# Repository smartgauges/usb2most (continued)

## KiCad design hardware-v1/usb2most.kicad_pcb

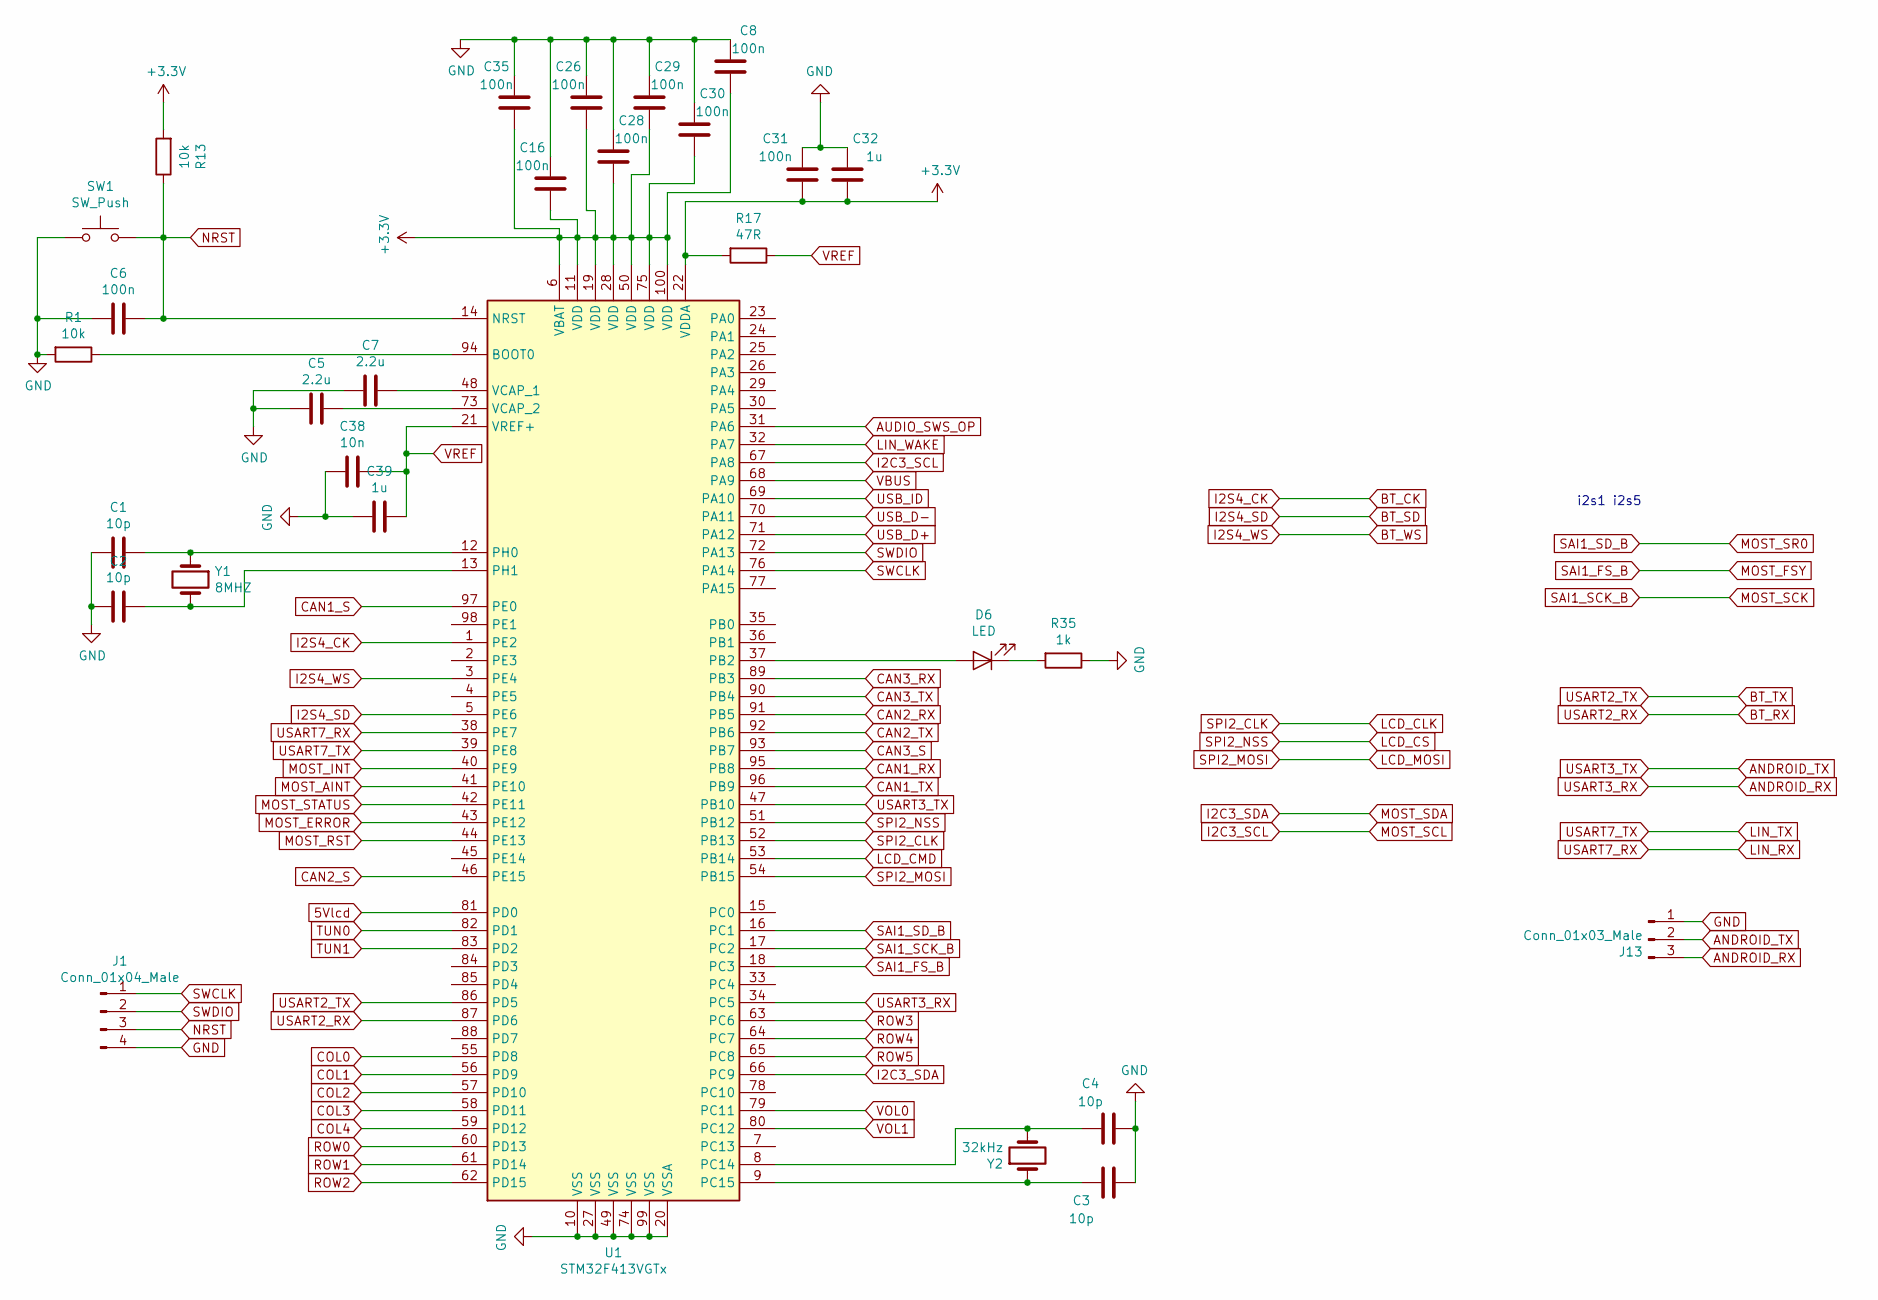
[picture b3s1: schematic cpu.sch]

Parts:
C1, C2, C3, C4: 10p; C_0805_2012Metric
C5, C7: 2.2u; C_1206_3216Metric
C6, C8, C16, C26, C28, C29, C30, C31, C35: 100n; C_0805_2012Metric
C32, C39: 1u; C_1206_3216Metric
C38: 10n; C_0805_2012Metric
D6: LED; R_0805_2012Metric
J1: Conn_01x04_Male; PinSocket_1x04_P2.54mm_Vertical
J13: Conn_01x03_Male; PinSocket_1x03_P2.54mm_Vertical
R1, R13: 10k; R_0805_2012Metric
R17: 47R; R_0805_2012Metric
R35: 1k; R_0805_2012Metric
SW1: SW_Push; SW_Push_1P1T_NO_6x6mm_H9.5mm
U1: STM32F413VGTx; LQFP-100_14x14mm_P0.5mm
Y1: 8MHZ; Crystal_HC49-U_Vertical
Y2: 32kHz; Crystal_C26-LF_D2.1mm_L6.5mm_Vertical

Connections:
5Vlcd: U1.81 (PD0); also elsewhere on the board
+3V3: C8.1, C16.1, C26.1, C28.1, C29.1, C30.1, C31.1, C32.1, C35.1, R13.2, R17.2, U1.6 (VBAT), U1.11 (VDD), U1.19 (VDD), U1.22 (VDDA), U1.28 (VDD), U1.50 (VDD), U1.75 (VDD), U1.100 (VDD); also elsewhere on the board
ANDROID_RX: J13.3, U1.34 (PC5)
ANDROID_TX: J13.2, U1.47 (PB10)
AUDIO_SWS_OP: U1.31 (PA6); also elsewhere on the board
BT_CK: U1.1 (PE2); also elsewhere on the board
BT_RX: U1.87 (PD6); also elsewhere on the board
BT_SD: U1.5 (PE6); also elsewhere on the board
BT_TX: U1.86 (PD5); also elsewhere on the board
BT_WS: U1.3 (PE4); also elsewhere on the board
CAN1_RX: U1.95 (PB8); also elsewhere on the board
CAN1_S: U1.97 (PE0); also elsewhere on the board
CAN1_TX: U1.96 (PB9); also elsewhere on the board
CAN2_RX: U1.91 (PB5); also elsewhere on the board
CAN2_S: U1.46 (PE15); also elsewhere on the board
CAN2_TX: U1.92 (PB6); also elsewhere on the board
CAN3_RX: U1.89 (PB3); also elsewhere on the board
CAN3_S: U1.93 (PB7); also elsewhere on the board
CAN3_TX: U1.90 (PB4); also elsewhere on the board
COL0: U1.55 (PD8); also elsewhere on the board
COL1: U1.56 (PD9); also elsewhere on the board
COL2: U1.57 (PD10); also elsewhere on the board
COL3: U1.58 (PD11); also elsewhere on the board
COL4: U1.59 (PD12); also elsewhere on the board
GND: C1.2, C2.2, C3.2, C4.2, C5.2, C6.2, C7.2, C8.2, C16.2, C26.2, C28.2, C29.2, C30.2, C31.2, C32.2, C35.2, C38.2, C39.2, J1.4, J13.1, R1.2, R35.1, SW1.1, U1.10 (VSS), U1.20 (VSSA), U1.27 (VSS), U1.49 (VSS), U1.74 (VSS), U1.99 (VSS); also elsewhere on the board
I2C1_SCL: U1.67 (PA8); also elsewhere on the board
I2C1_SDA: U1.66 (PC9); also elsewhere on the board
LCD_CLK: U1.52 (PB13); also elsewhere on the board
LCD_CMD: U1.53 (PB14); also elsewhere on the board
LCD_CS: U1.51 (PB12); also elsewhere on the board
LCD_MOSI: U1.54 (PB15); also elsewhere on the board
LIN_RX: U1.38 (PE7); also elsewhere on the board
LIN_TX: U1.39 (PE8); also elsewhere on the board
LIN_WAKE: U1.32 (PA7); also elsewhere on the board
MOST_AINT: U1.41 (PE10); also elsewhere on the board
MOST_ERROR: U1.43 (PE12); also elsewhere on the board
MOST_FSY: U1.18 (PC3); also elsewhere on the board
MOST_INT: U1.40 (PE9); also elsewhere on the board
MOST_RST: U1.44 (PE13); also elsewhere on the board
MOST_SCK: U1.17 (PC2); also elsewhere on the board
MOST_SR0: U1.16 (PC1); also elsewhere on the board
MOST_STATUS: U1.42 (PE11); also elsewhere on the board
NRST: C6.1, J1.3, R13.1, SW1.2, U1.14 (NRST)
unnamed: C1.1, U1.12 (PH0), Y1.1
unnamed: C2.1, U1.13 (PH1), Y1.2
unnamed: C3.1, U1.9 (PC15), Y2.1
unnamed: C4.1, U1.8 (PC14), Y2.2
unnamed: C5.1, U1.73 (VCAP_2)
unnamed: C7.1, U1.48 (VCAP_1)
unnamed: D6.1 (K), R35.2
unnamed: D6.2 (A), U1.37 (PB2)
unnamed: R1.1, U1.94 (BOOT0)
ROW0: U1.60 (PD13); also elsewhere on the board
ROW1: U1.61 (PD14); also elsewhere on the board
ROW2: U1.62 (PD15); also elsewhere on the board
ROW3: U1.63 (PC6); also elsewhere on the board
ROW4: U1.64 (PC7); also elsewhere on the board
ROW5: U1.65 (PC8); also elsewhere on the board
SWCLK: J1.1, U1.76 (PA14)
SWDIO: J1.2, U1.72 (PA13)
TUN0: U1.82 (PD1); also elsewhere on the board
TUN1: U1.83 (PD2); also elsewhere on the board
USB_D+: U1.71 (PA12); also elsewhere on the board
USB_D-: U1.70 (PA11); also elsewhere on the board
USB_ID: U1.69 (PA10); also elsewhere on the board
VBUS: U1.68 (PA9); also elsewhere on the board
VOL0: U1.79 (PC11); also elsewhere on the board
VOL1: U1.80 (PC12); also elsewhere on the board
VREF: C38.1, C39.1, R17.1, U1.21 (VREF+)

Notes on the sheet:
i2s1 i2s5

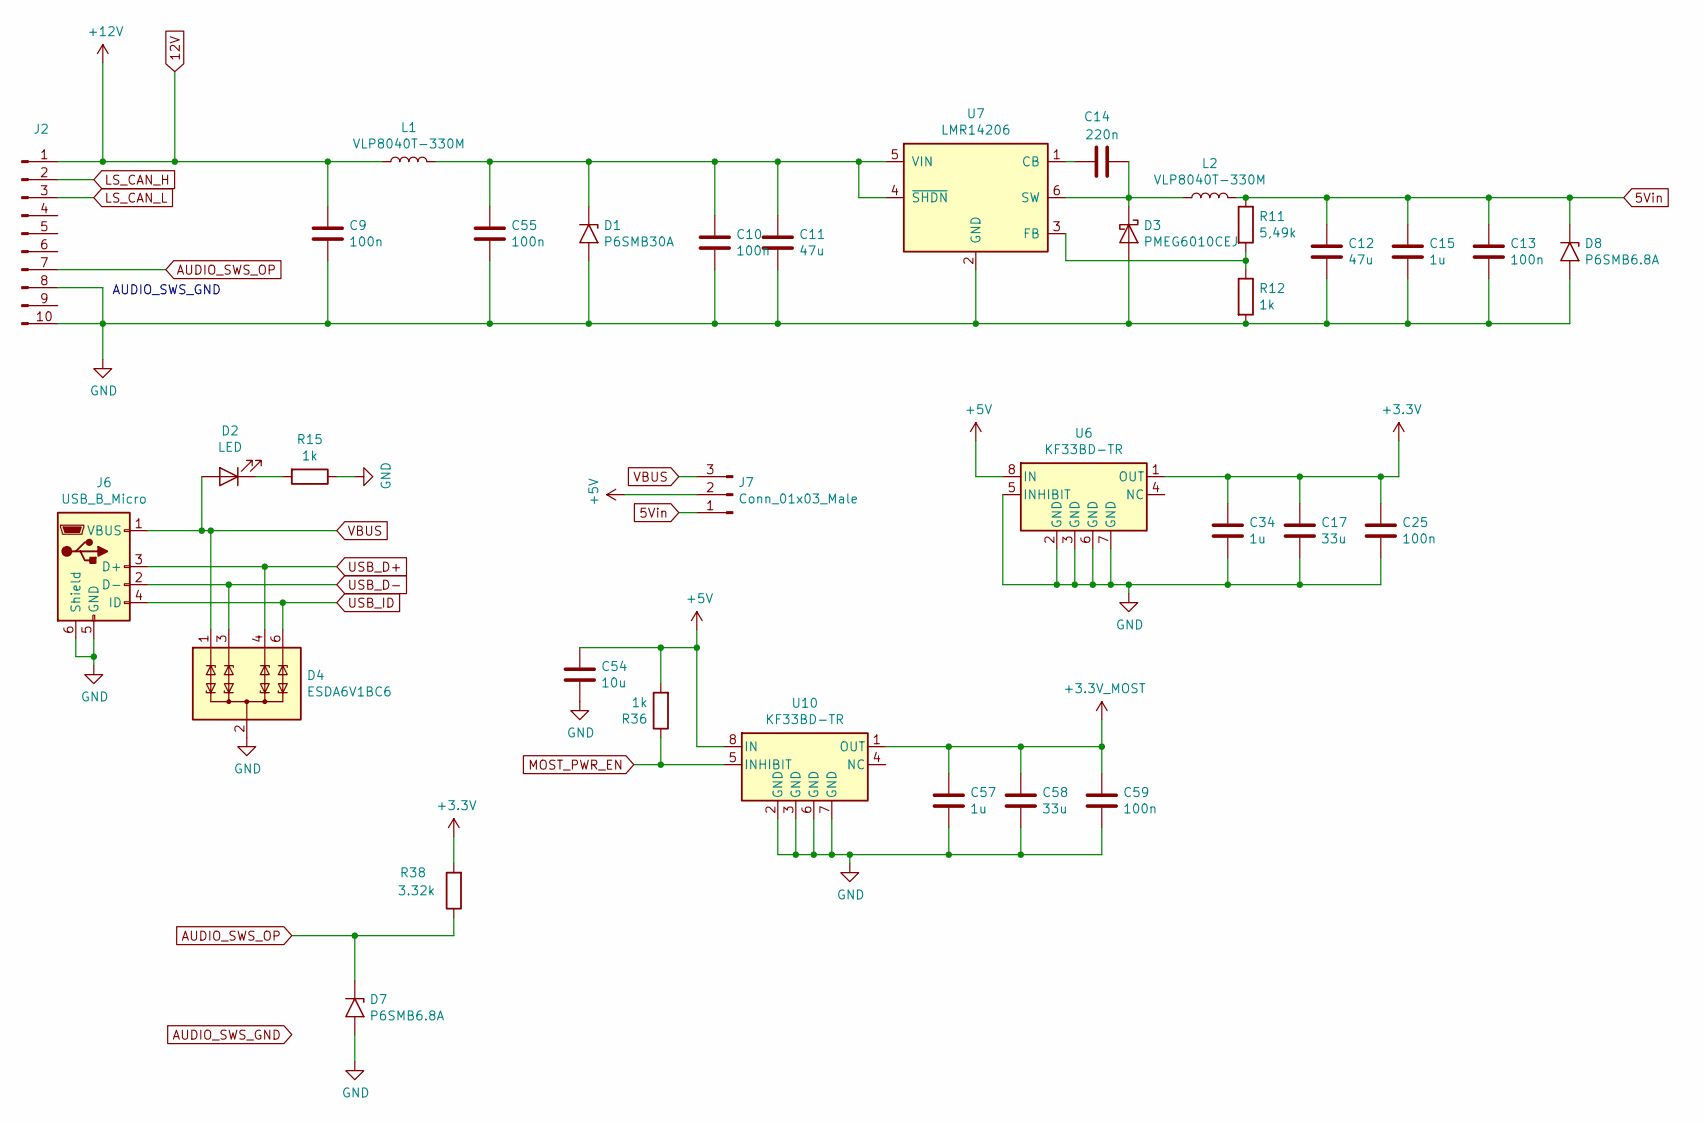
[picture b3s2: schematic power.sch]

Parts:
C9, C10, C13, C25, C55, C59: 100n; C_0805_2012Metric
C11, C12: 47u; C_1206_3216Metric
C14: 220n; C_0805_2012Metric
C15, C34, C57: 1u; C_1206_3216Metric
C17, C58: 33u; C_1206_3216Metric
C54: 10u; C_1206_3216Metric
D1: P6SMB30A; D_SMB
D2: LED; R_0805_2012Metric
D3: PMEG6010CEJ; D_SOD-323
D4: ESDA6V1BC6; SOT-23-6
D7, D8: P6SMB6.8A; D_SMB
J2: Conn_01x10_Male; IL-AG5-10P-S3L2
J6: USB_B_Micro; USB_Micro-B_Molex-105133-0031
J7: Conn_01x03_Male; PinSocket_1x03_P2.54mm_Vertical
L1, L2: VLP8040T-330M; L_TDK_VLP8040
R11: 5,49k; R_0805_2012Metric
R12, R15, R36: 1k; R_0805_2012Metric
R38: 3.32k; R_0805_2012Metric
U6, U10: KF33BD-TR; SO-8_5.3x6.2mm_P1.27mm
U7: LMR14206; SOT-23-6

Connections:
5Vin: C12.1, C13.1, C15.1, D8.1 (A1), J7.1, L2.2, R11.1
12V: C9.1, J2.1, L1.1; also elsewhere on the board
+3.3_MOST: C57.1, C58.1, C59.1, U10.1 (OUT); also elsewhere on the board
+3V3: C17.1, C25.1, C34.1, R38.2, U6.1 (OUT); also elsewhere on the board
+5V: C54.1, J7.2, R36.2, U6.8 (IN), U10.8 (IN); also elsewhere on the board
AUDIO_SWS_OP: D7.1 (A1), J2.7, R38.1; also elsewhere on the board
GND: C9.2, C10.2, C11.2, C12.2, C13.2, C15.2, C17.2, C25.2, C34.2, C54.2, C55.2, C57.2, C58.2, C59.2, D1.2 (A2), D3.2 (A), D4.2 (COM), D4.5 (COM), D7.2 (A2), D8.2 (A2), J2.8, J2.10, J6.5 (GND), J6.6 (Shield), R12.2, R15.1, U6.2 (GND), U6.3 (GND), U6.5 (INHIBIT), U6.6 (GND), U6.7 (GND), U7.2 (GND), U10.2 (GND), U10.3 (GND), U10.6 (GND), U10.7 (GND); also elsewhere on the board
LS_CAN_H: J2.2; also elsewhere on the board
LS_CAN_L: J2.3; also elsewhere on the board
MOST_PWR_EN: R36.1, U10.5 (INHIBIT)
unnamed: C10.1, C11.1, C55.1, D1.1 (A1), L1.2, U7.4 (~SHDN), U7.5 (VIN)
unnamed: C14.1, U7.1 (CB)
unnamed: C14.2, D3.1 (K), L2.1, U7.6 (SW)
unnamed: D2.1 (K), R15.2
unnamed: R11.2, R12.1, U7.3 (FB)
USB_D+: D4.4 (TVS3), J6.3 (D+); also elsewhere on the board
USB_D-: D4.3 (TVS2), J6.2 (D-); also elsewhere on the board
USB_ID: D4.6 (TVS4), J6.4 (ID); also elsewhere on the board
VBUS: D2.2 (A), D4.1 (TVS1), J6.1 (VBUS), J7.3; also elsewhere on the board

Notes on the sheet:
AUDIO_SWS_GND

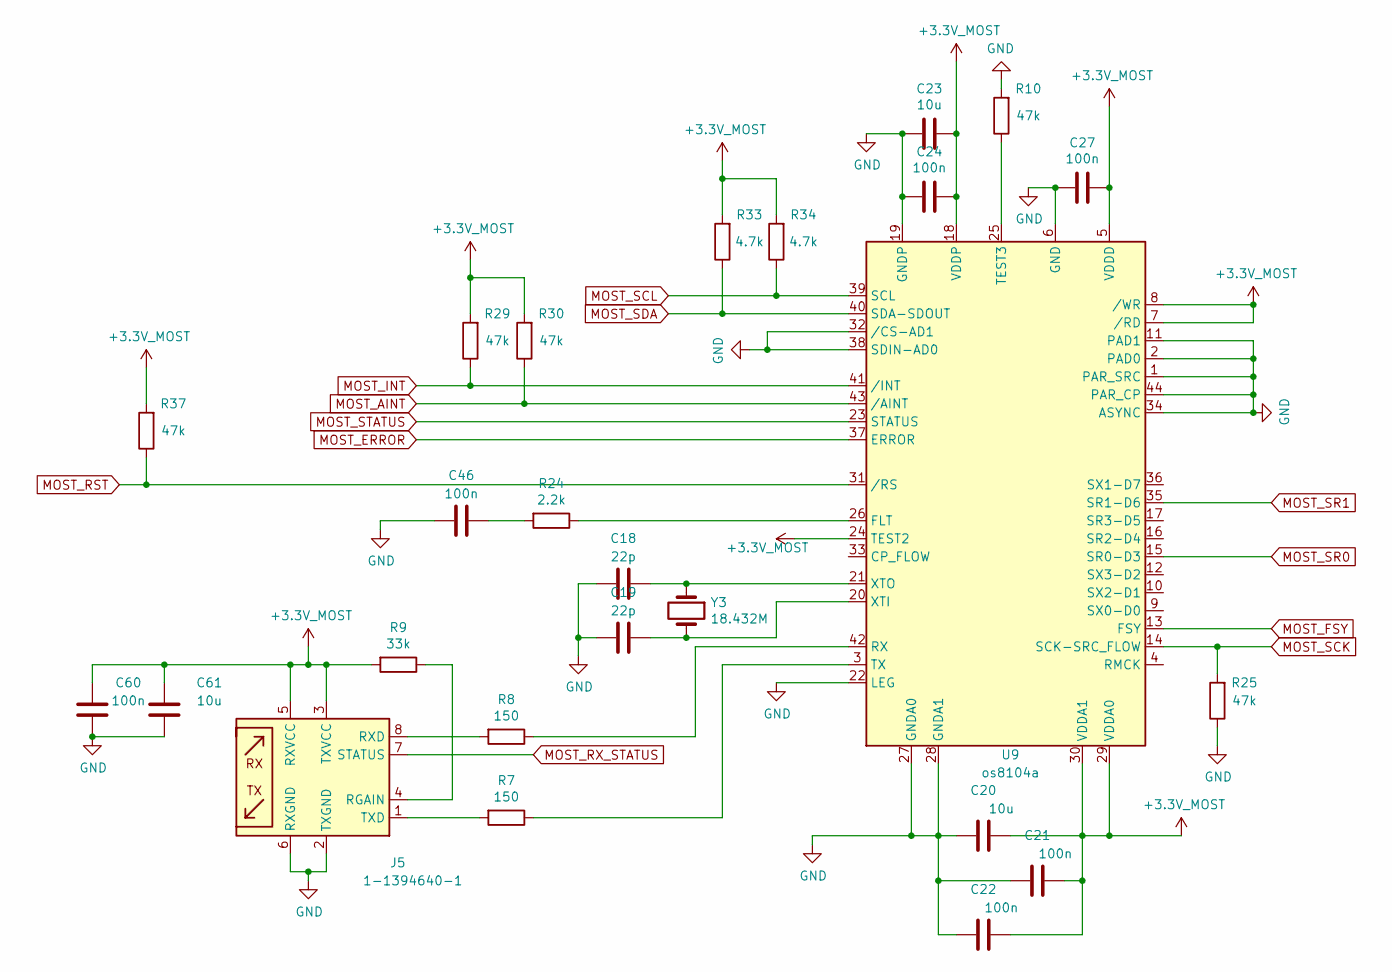
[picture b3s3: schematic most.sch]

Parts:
C18, C19: 22p; C_0805_2012Metric
C20, C23, C61: 10u; C_1206_3216Metric
C21, C22, C24, C27, C46, C60: 100n; C_0805_2012Metric
J5: 1-1394640-1; TYCO_1_1394640_1
R7, R8: 150; R_0805_2012Metric
R9: 33k; R_0805_2012Metric
R10, R25, R29, R30, R37: 47k; R_0805_2012Metric
R24: 2.2k; R_0805_2012Metric
R33, R34: 4.7k; R_0805_2012Metric
U9: os8104a; LQFP-44_10x10mm_P0.8mm
Y3: 18.432M; Crystal_HC49-U_Vertical

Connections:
+3.3_MOST: C20.1, C21.1, C22.1, C23.1, C24.1, C27.1, C60.2, C61.2, J5.3 (TXVCC), J5.5 (RXVCC), R9.2, R29.2, R30.2, R33.2, R34.2, R37.2, U9.5 (VDDD), U9.7 (/RD), U9.8 (/WR), U9.18 (VDDP), U9.24 (TEST2), U9.29 (VDDA0), U9.30 (VDDA1); also elsewhere on the board
GND: C18.2, C19.2, C20.2, C21.2, C22.2, C23.2, C24.2, C27.2, C46.2, C60.1, C61.1, J5.2 (TXGND), J5.6 (RXGND), R10.2, R25.1, U9.1 (PAR_SRC), U9.2 (PAD0), U9.6 (GND), U9.11 (PAD1), U9.19 (GNDP), U9.22 (LEG), U9.27 (GNDA0), U9.28 (GNDA1), U9.32 (/CS-AD1), U9.34 (ASYNC), U9.38 (SDIN-AD0), U9.44 (PAR_CP); also elsewhere on the board
I2C1_SCL: R34.1, U9.39 (SCL); also elsewhere on the board
I2C1_SDA: R33.1, U9.40 (SDA-SDOUT); also elsewhere on the board
MOST_AINT: R30.1, U9.43 (/AINT); also elsewhere on the board
MOST_ERROR: U9.37 (ERROR); also elsewhere on the board
MOST_FSY: U9.13 (FSY); also elsewhere on the board
MOST_INT: R29.1, U9.41 (/INT); also elsewhere on the board
MOST_RST: R37.1, U9.31 (/RS); also elsewhere on the board
MOST_RX_STATUS: J5.7 (STATUS)
MOST_SCK: R25.2, U9.14 (SCK-SRC_FLOW); also elsewhere on the board
MOST_SR0: U9.15 (SR0-D3); also elsewhere on the board
MOST_SR1: U9.35 (SR1-D6)
MOST_STATUS: U9.23 (STATUS); also elsewhere on the board
unnamed: C18.1, U9.21 (XTO), Y3.1
unnamed: C19.1, U9.20 (XTI), Y3.2
unnamed: C46.1, R24.2
unnamed: J5.1 (TXD), R7.2
unnamed: J5.4 (RGAIN), R9.1
unnamed: J5.8 (RXD), R8.2
unnamed: R7.1, U9.3 (TX)
unnamed: R8.1, U9.42 (RX)
unnamed: R10.1, U9.25 (TEST3)
unnamed: R24.1, U9.26 (FLT)

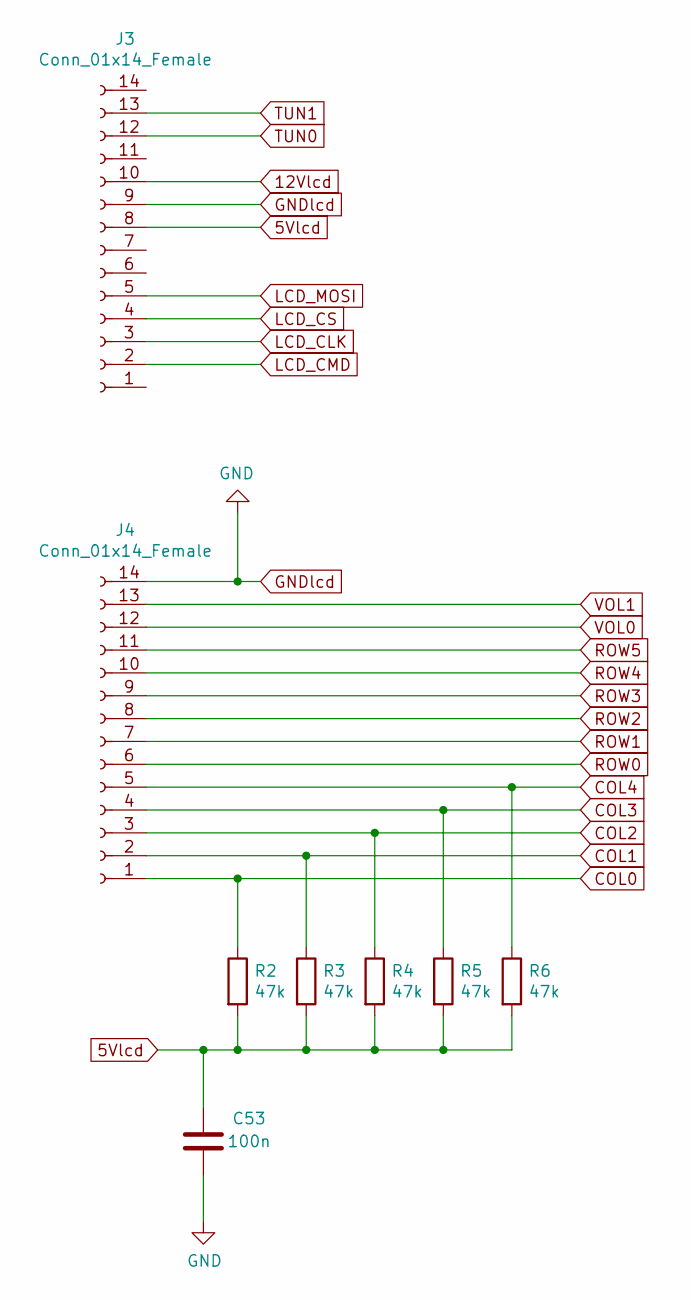
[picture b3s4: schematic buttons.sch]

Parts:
C53: 100n; C_0805_2012Metric
J3, J4: Conn_01x14_Female; 1x14-2.00mm
R2, R3, R4, R5, R6: 47k; R_0805_2012Metric

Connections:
5Vlcd: C53.2, J3.8, R2.2, R3.2, R4.2, R5.2, R6.2; also elsewhere on the board
12Vlcd: J3.10
COL0: J4.1, R2.1; also elsewhere on the board
COL1: J4.2, R3.1; also elsewhere on the board
COL2: J4.3, R4.1; also elsewhere on the board
COL3: J4.4, R5.1; also elsewhere on the board
COL4: J4.5, R6.1; also elsewhere on the board
GND: C53.1, J3.9, J4.14; also elsewhere on the board
LCD_CLK: J3.3; also elsewhere on the board
LCD_CMD: J3.2; also elsewhere on the board
LCD_CS: J3.4; also elsewhere on the board
LCD_MOSI: J3.5; also elsewhere on the board
ROW0: J4.6; also elsewhere on the board
ROW1: J4.7; also elsewhere on the board
ROW2: J4.8; also elsewhere on the board
ROW3: J4.9; also elsewhere on the board
ROW4: J4.10; also elsewhere on the board
ROW5: J4.11; also elsewhere on the board
TUN0: J3.12; also elsewhere on the board
TUN1: J3.13; also elsewhere on the board
VOL0: J4.12; also elsewhere on the board
VOL1: J4.13; also elsewhere on the board

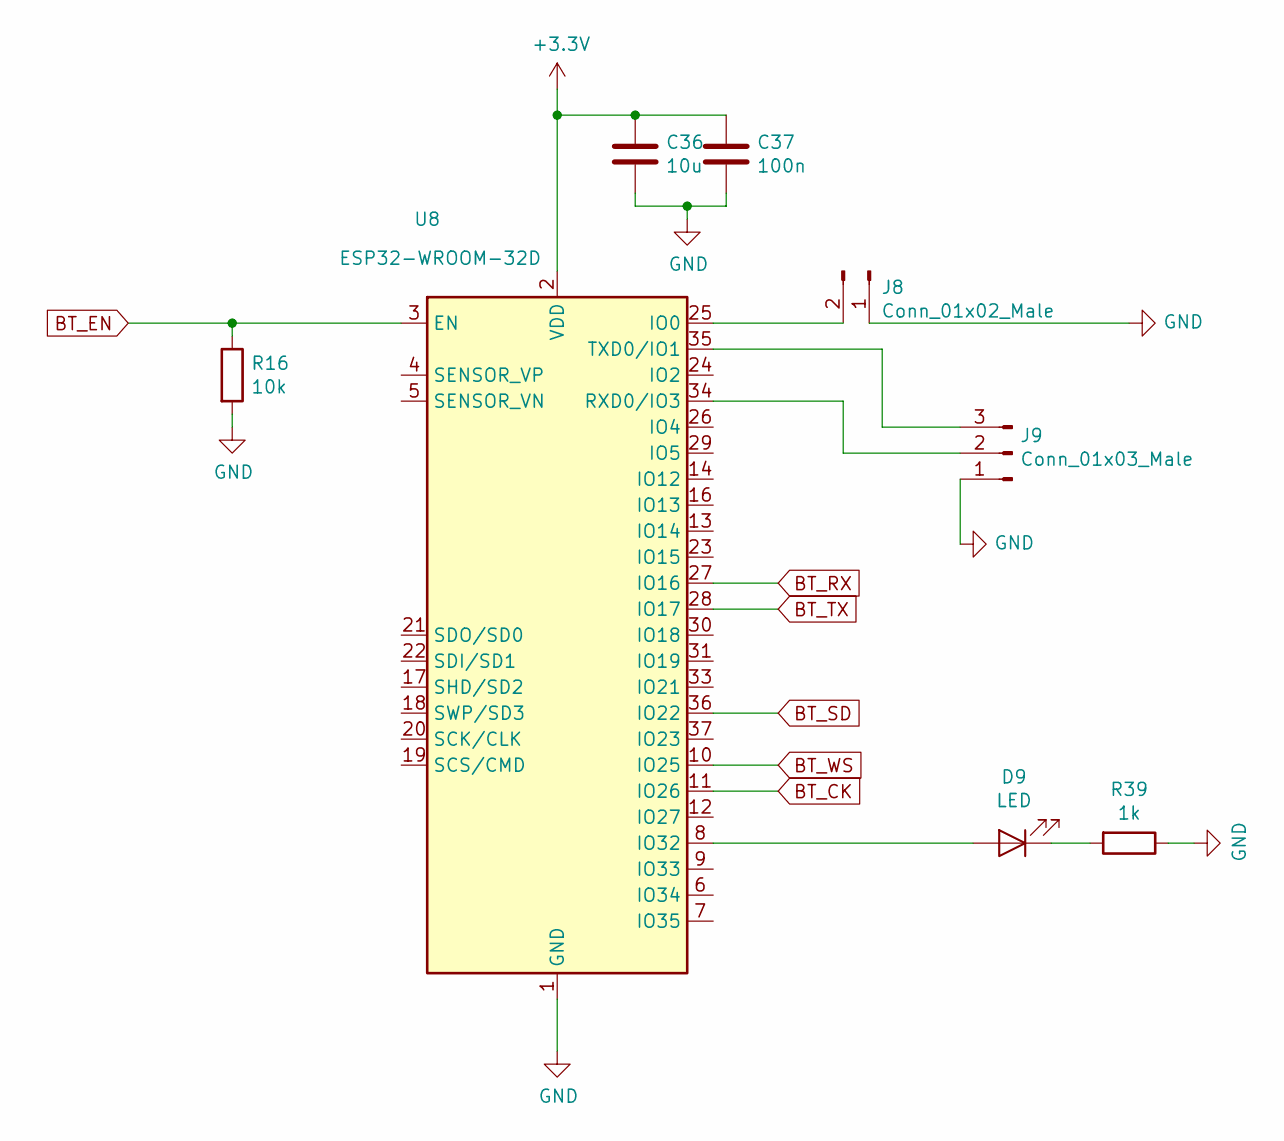
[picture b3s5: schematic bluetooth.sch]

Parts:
C36: 10u; C_1206_3216Metric
C37: 100n; C_0805_2012Metric
D9: LED; R_0805_2012Metric
J8: Conn_01x02_Male; PinSocket_1x02_P2.54mm_Vertical
J9: Conn_01x03_Male; PinSocket_1x03_P2.54mm_Vertical
R16: 10k; R_0805_2012Metric
R39: 1k; R_0805_2012Metric
U8: ESP32-WROOM-32D; ESP32-WROOM-32

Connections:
+3V3: C36.1, C37.1, U8.2 (VDD); also elsewhere on the board
BT_CK: U8.11 (IO26); also elsewhere on the board
BT_EN: R16.1, U8.3 (EN)
BT_RX: U8.27 (IO16); also elsewhere on the board
BT_SD: U8.36 (IO22); also elsewhere on the board
BT_TX: U8.28 (IO17); also elsewhere on the board
BT_WS: U8.10 (IO25); also elsewhere on the board
GND: C36.2, C37.2, J8.1, J9.1, R16.2, R39.1, U8.1 (GND), U8.15 (GND), U8.38 (GND); also elsewhere on the board
unnamed: D9.1 (K), R39.2
unnamed: D9.2 (A), U8.8 (IO32)
unnamed: J8.2, U8.25 (IO0)
unnamed: J9.2, U8.34 (RXD0/IO3)
unnamed: J9.3, U8.35 (TXD0/IO1)

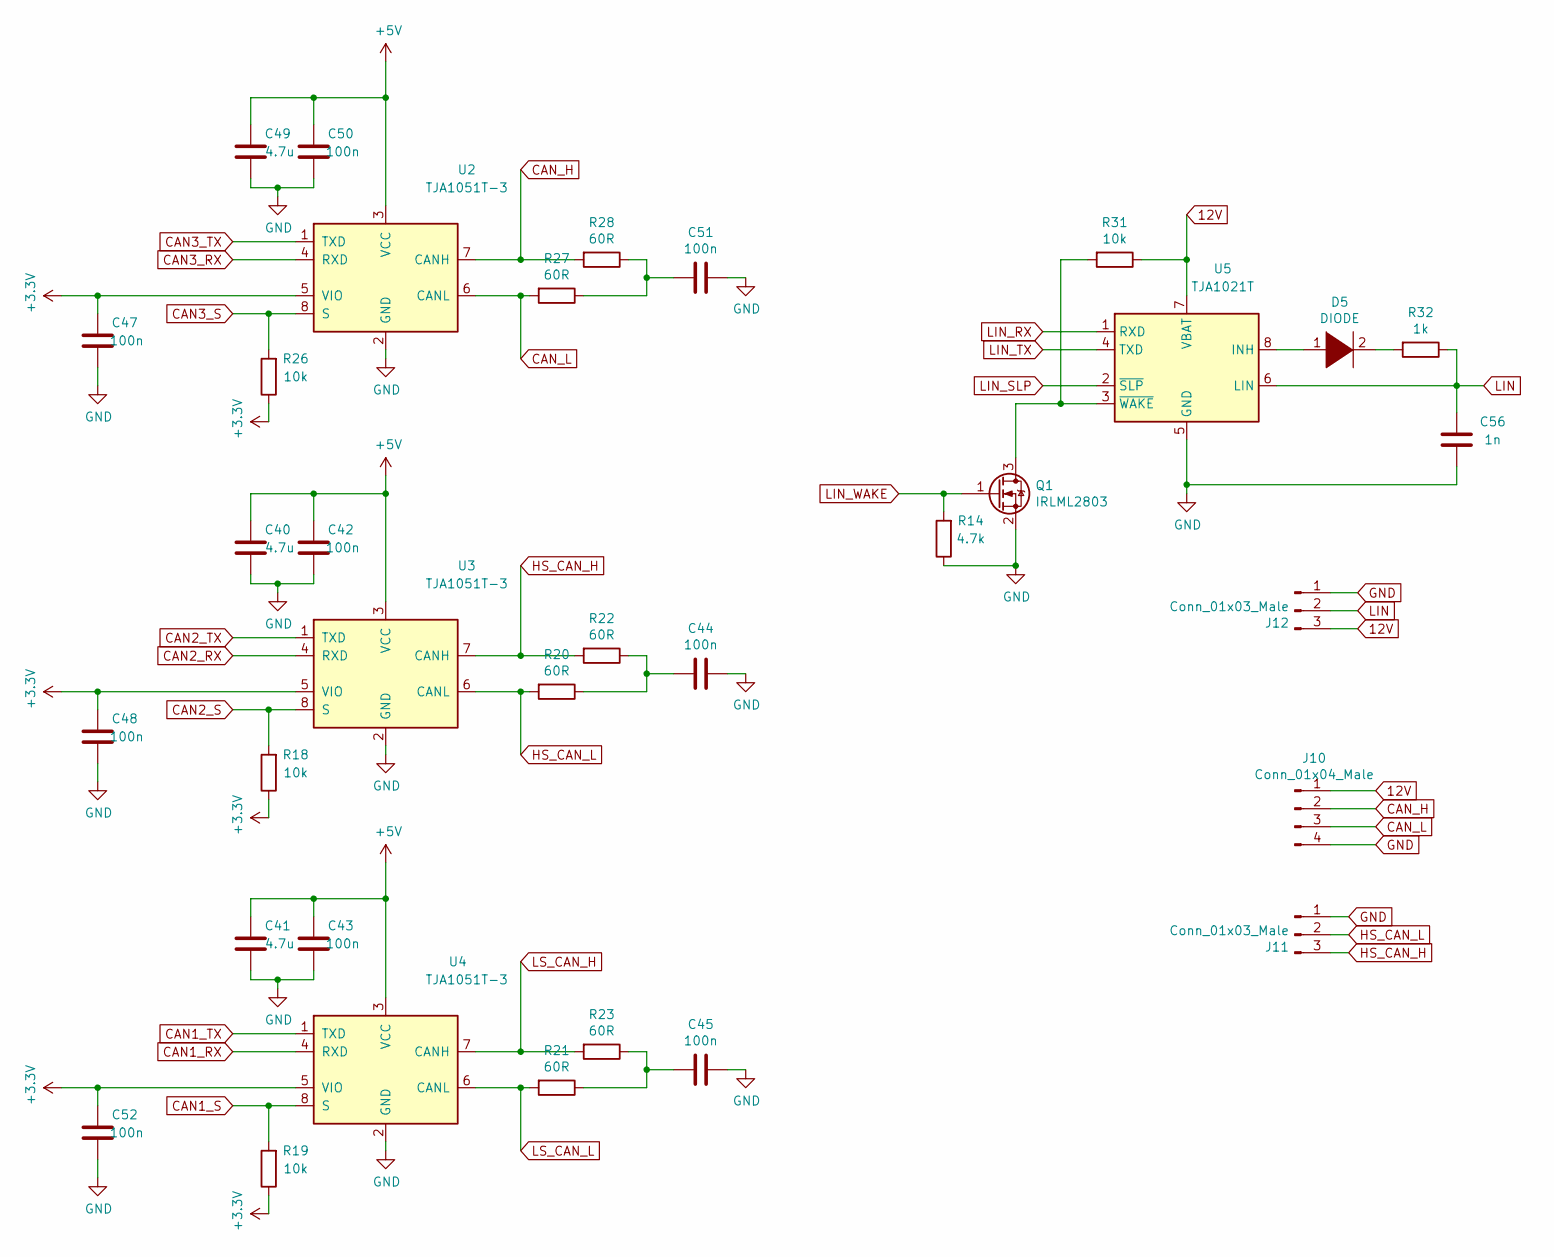
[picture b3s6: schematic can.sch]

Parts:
C40, C41, C49: 4.7u; C_1206_3216Metric
C42, C43, C44, C45, C47, C48, C50, C51, C52: 100n; C_0805_2012Metric
C56: 1n; C_0805_2012Metric
D5: DIODE; R_0805_2012Metric
J10: Conn_01x04_Male; PinSocket_1x04_P2.54mm_Vertical
J11, J12: Conn_01x03_Male; PinSocket_1x03_P2.54mm_Vertical
Q1: IRLML2803; SOT-23
R14: 4.7k; R_0805_2012Metric
R18, R19, R26, R31: 10k; R_0805_2012Metric
R20, R21, R22, R23, R27, R28: 60R; R_0805_2012Metric
R32: 1k; R_0805_2012Metric
U2, U3, U4: TJA1051T-3; SOIC-8_3.9x4.9mm_P1.27mm
U5: TJA1021T; SOIC-8_3.9x4.9mm_P1.27mm

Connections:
12V: J10.1, J12.3, R31.1, U5.7 (VBAT); also elsewhere on the board
+3V3: C47.2, C48.2, C52.2, R18.1, R19.1, R26.1, U2.5 (VIO), U3.5 (VIO), U4.5 (VIO); also elsewhere on the board
+5V: C40.2, C41.2, C42.2, C43.2, C49.2, C50.2, U2.3 (VCC), U3.3 (VCC), U4.3 (VCC); also elsewhere on the board
CAN1_RX: U4.4 (RXD); also elsewhere on the board
CAN1_S: R19.2, U4.8 (S); also elsewhere on the board
CAN1_TX: U4.1 (TXD); also elsewhere on the board
CAN2_RX: U3.4 (RXD); also elsewhere on the board
CAN2_S: R18.2, U3.8 (S); also elsewhere on the board
CAN2_TX: U3.1 (TXD); also elsewhere on the board
CAN3_RX: U2.4 (RXD); also elsewhere on the board
CAN3_S: R26.2, U2.8 (S); also elsewhere on the board
CAN3_TX: U2.1 (TXD); also elsewhere on the board
CAN_H: J10.2, R28.2, U2.7 (CANH)
CAN_L: J10.3, R27.2, U2.6 (CANL)
GND: C40.1, C41.1, C42.1, C43.1, C44.1, C45.1, C47.1, C48.1, C49.1, C50.1, C51.1, C52.1, C56.1, J10.4, J11.1, J12.1, Q1.2 (S), R14.1, U2.2 (GND), U3.2 (GND), U4.2 (GND), U5.5 (GND); also elsewhere on the board
HS_CAN_H: J11.3, R22.2, U3.7 (CANH)
HS_CAN_L: J11.2, R20.2, U3.6 (CANL)
LIN: C56.2, J12.2, R32.1, U5.6 (LIN)
LIN_RX: U5.1 (RXD); also elsewhere on the board
LIN_SLP: U5.2 (~SLP~)
LIN_TX: U5.4 (TXD); also elsewhere on the board
LIN_WAKE: Q1.1 (G), R14.2; also elsewhere on the board
LS_CAN_H: R23.2, U4.7 (CANH); also elsewhere on the board
LS_CAN_L: R21.2, U4.6 (CANL); also elsewhere on the board
unnamed: C44.2, R20.1, R22.1
unnamed: C45.2, R21.1, R23.1
unnamed: C51.2, R27.1, R28.1
unnamed: D5.1 (K), U5.8 (INH)
unnamed: D5.2 (A), R32.2
unnamed: Q1.3 (D), R31.2, U5.3 (~WAKE~)

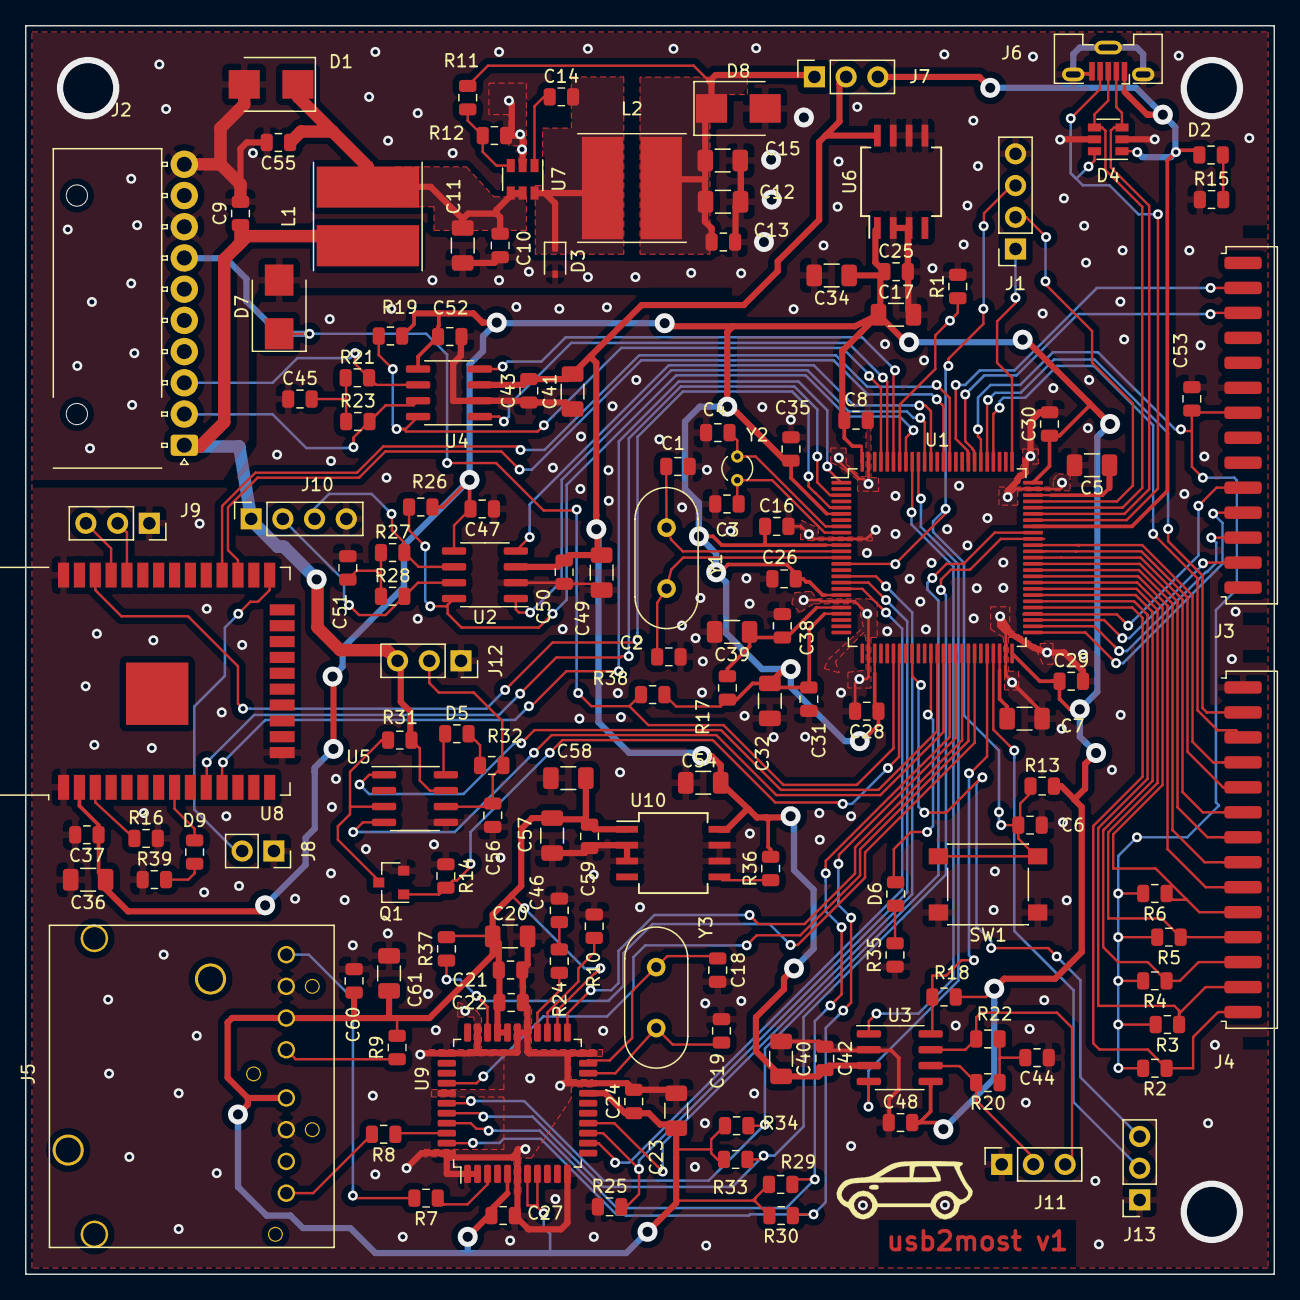
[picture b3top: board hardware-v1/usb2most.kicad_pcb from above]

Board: 2 copper layers, 100.0 x 100.0 mm, 138 parts (0 on the bottom side), 108 nets.

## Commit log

2019-08-29 Create LICENSE
2019-08-29 added hardware files
2019-08-29 added pcb image
2019-08-29 modified readme
2020-04-05 added hardware files v2
2020-10-16 added hardware files v3
2020-10-16 added hardware files for adapter-lr2
2020-10-16 added schematic file in pdf format
2020-10-27 added a photo of the boardv3
2020-11-02 added firmware ver1 files and android application
2020-11-03 added cdcacm.inf file and win32 application
2020-11-03 added firmware ver2 files(fixed numeration of endpoints for windows)
2020-11-08 added firmware ver2 file in dfu format
2020-11-26 added firmware ver3 files and updated win32 app
2020-12-01 added firmware ver4 files and updated win32 app
2020-12-08 added firmware ver5 files and updated win32 and android apps
2020-12-11 added firmware ver6 files and updated win32 and android apps
2020-12-12 added firmware ver7 files
2020-12-14 updated android app
2020-12-15 added firmware ver8 files and updated win32 and android apps
2020-12-15 added firmware ver9 files
2020-12-15 added firmware ver10 files
2021-01-02 added firmware ver11 files and updated android app
2021-01-07 added firmware ver12 file and updated android app
2021-01-13 updated win32 app
2021-02-05 added firmware ver13 file and updated android app
2021-02-05 Oops
2021-02-28 added firmware ver14 file and updated android and win32 apps
2021-04-12 added firmware ver15 and ver16 files
2021-06-21 added firmware ver17 file and updated android and win32 apps
2021-07-11 added firmware ver18 file and updated android app
2021-10-14 added firmware ver19 file and updated android and win32 apps
2021-12-10 added firmware ver20 files and updated android and win32 apps
2022-01-28 added firmware ver21 files and updated android and win32 apps
2022-04-17 added firmware ver22 files and updated android and win32 apps
2022-04-18 added firmware ver22 files(oops)
2022-08-08 added firmware ver23 files and updated android and win32 apps
2022-08-08 changed mode bits for panel.exe
2023-05-09 added firmware ver24 files and updated android and win32 apps
2025-02-22 added sources for android widget
2025-04-22 added miniapp for android, which is compiled from sources from the android directory
